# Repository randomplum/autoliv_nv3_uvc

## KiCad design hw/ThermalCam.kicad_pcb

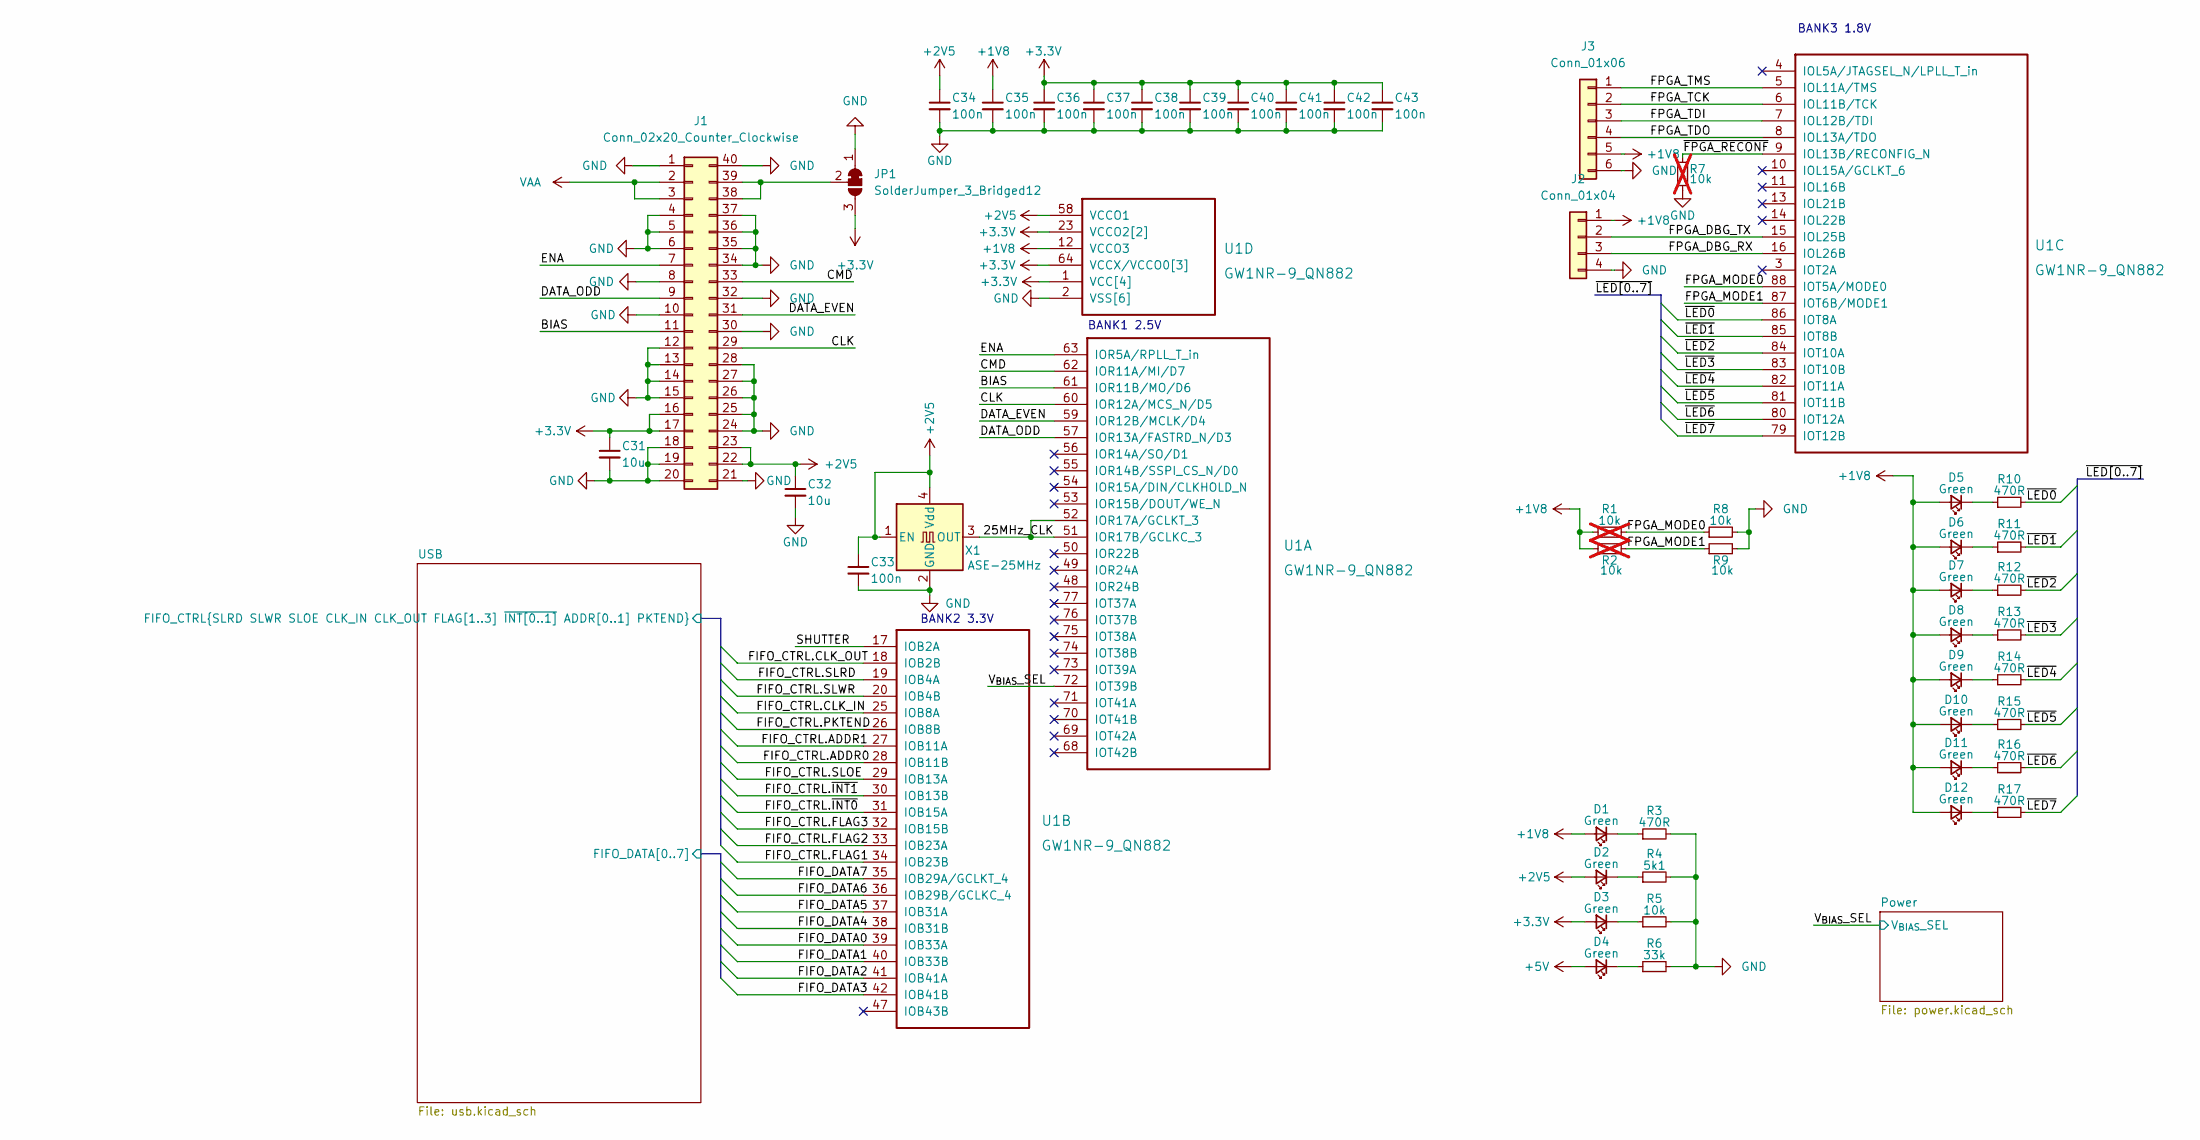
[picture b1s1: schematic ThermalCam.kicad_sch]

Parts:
C31, C32: 10u; C_0402_1005Metric
C33, C34, C35, C36, C37, C38, C39, C40, C41, C42, C43: 100n; C_0402_1005Metric
D1, D2, D3, D4, D5, D6, D7, D8, D9, D10, D11, D12: Green; LED_0402_1005Metric
J1: Conn_02x20_Counter_Clockwise; 52991-0408
J2: Conn_01x04; PinHeader_1x04_P2.54mm_Vertical
J3: Conn_01x06; PinHeader_1x06_P2.54mm_Vertical
JP1: SolderJumper_3_Bridged12; SolderJumper-3_P1.3mm_Bridged2Bar12_RoundedPad1.0x1.5mm_Num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
R1, R2, R7: 10k; R_0402_1005Metric; not fitted
R3, R10, R11, R12, R13, R14, R15, R16, R17: 470R; R_0402_1005Metric
R4: 5k1; R_0402_1005Metric
R5, R8, R9: 10k; R_0402_1005Metric
R6: 33k; R_0402_1005Metric
U1: GW1NR-9_QN882; QFN-88_EP_10x10_Pitch0.4mm
X1: ASE-25MHz; Oscillator_SMD_Abracon_ASE-4Pin_3.2x2.5mm

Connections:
+1V8: C35.1, D1.2 (A), D5.2 (A), D6.2 (A), D7.2 (A), D8.2 (A), D9.2 (A), D10.2 (A), D11.2 (A), D12.2 (A), J2.1, J3.5, R1.1, R2.1, U1.12 (VCCO3); also elsewhere on the board
+2V5: C32.1, C33.1, C34.1, D2.2 (A), J1.22, J1.23, U1.58 (VCCO1), X1.1 (EN), X1.4 (Vdd); also elsewhere on the board
+3.3V: C31.1, C36.1, C37.1, C38.1, C39.1, C40.1, C41.1, C42.1, C43.1, D3.2 (A), J1.16, J1.17, JP1.3 (B), U1.1 (VCC[4]), U1.22 (VCC[4]), U1.23 (VCCO2[2]), U1.44 (VCCO2[2]), U1.45 (VCC[4]), U1.64 (VCCX/VCCO0[3]), U1.66 (VCC[4]), U1.67 (VCCX/VCCO0[3]), U1.78 (VCCX/VCCO0[3]); also elsewhere on the board
+5V: D4.2 (A); also elsewhere on the board
/25MHz_CLK: U1.51 (IOR17B/GCLKC_3), U1.52 (IOR17A/GCLKT_3), X1.3 (OUT)
/BIAS: J1.11, U1.61 (IOR11B/MO/D6)
/CLK: J1.29, U1.60 (IOR12A/MCS_N/D5)
/CMD: J1.33, U1.62 (IOR11A/MI/D7)
/DATA_EVEN: J1.31, U1.59 (IOR12B/MCLK/D4)
/DATA_ODD: J1.9, U1.57 (IOR13A/FASTRD_N/D3)
/ENA: J1.7, U1.63 (IOR5A/RPLL_T_in)
/FPGA_DBG_RX: J2.3, U1.16 (IOL26B)
/FPGA_DBG_TX: J2.2, U1.15 (IOL25B)
/FPGA_MODE0: R1.2, R8.1, U1.88 (IOT5A/MODE0)
/FPGA_MODE1: R2.2, R9.1, U1.87 (IOT6B/MODE1)
/FPGA_TCK: J3.2, U1.6 (IOL11B/TCK)
/FPGA_TDI: J3.3, U1.7 (IOL12B/TDI)
/FPGA_TDO: J3.4, U1.8 (IOL13A/TDO)
/FPGA_TMS: J3.1, U1.5 (IOL11A/TMS)
/SHUTTER: U1.17 (IOB2A)
/USB/FIFO_CTRL.ADDR0: U1.28 (IOB11B); also elsewhere on the board
/USB/FIFO_CTRL.ADDR1: U1.27 (IOB11A); also elsewhere on the board
/USB/FIFO_CTRL.CLK_IN: U1.25 (IOB8A); also elsewhere on the board
/USB/FIFO_CTRL.CLK_OUT: U1.18 (IOB2B); also elsewhere on the board
/USB/FIFO_CTRL.FLAG1: U1.34 (IOB23B); also elsewhere on the board
/USB/FIFO_CTRL.FLAG2: U1.33 (IOB23A); also elsewhere on the board
/USB/FIFO_CTRL.FLAG3: U1.32 (IOB15B); also elsewhere on the board
/USB/FIFO_CTRL.PKTEND: U1.26 (IOB8B); also elsewhere on the board
/USB/FIFO_CTRL.SLOE: U1.29 (IOB13A); also elsewhere on the board
/USB/FIFO_CTRL.SLRD: U1.19 (IOB4A); also elsewhere on the board
/USB/FIFO_CTRL.SLWR: U1.20 (IOB4B); also elsewhere on the board
/USB/FIFO_CTRL.~INT0: U1.31 (IOB15A); also elsewhere on the board
/USB/FIFO_CTRL.~INT1: U1.30 (IOB13B); also elsewhere on the board
/USB/FIFO_DATA0: U1.39 (IOB33A); also elsewhere on the board
/USB/FIFO_DATA1: U1.40 (IOB33B); also elsewhere on the board
/USB/FIFO_DATA2: U1.41 (IOB41A); also elsewhere on the board
/USB/FIFO_DATA3: U1.42 (IOB41B); also elsewhere on the board
/USB/FIFO_DATA4: U1.38 (IOB31B); also elsewhere on the board
/USB/FIFO_DATA5: U1.37 (IOB31A); also elsewhere on the board
/USB/FIFO_DATA6: U1.36 (IOB29B/GCLKC_4); also elsewhere on the board
/USB/FIFO_DATA7: U1.35 (IOB29A/GCLKT_4); also elsewhere on the board
/V_{BIAS}_SEL: U1.72 (IOT39B); also elsewhere on the board
/~FPGA_RECONF: R7.1, U1.9 (IOL13B/RECONFIG_N)
/~LED0: R10.2, U1.86 (IOT8A)
/~LED1: R11.2, U1.85 (IOT8B)
/~LED2: R12.2, U1.84 (IOT10A)
/~LED3: R13.2, U1.83 (IOT10B)
/~LED4: R14.2, U1.82 (IOT11A)
/~LED5: R15.2, U1.81 (IOT11B)
/~LED6: R16.2, U1.80 (IOT12A)
/~LED7: R17.2, U1.79 (IOT12B)
GND: C31.2, C32.2, C33.2, C34.2, C35.2, C36.2, C37.2, C38.2, C39.2, C40.2, C41.2, C42.2, C43.2, J1.1, J1.4, J1.5, J1.6, J1.8, J1.10, J1.12, J1.13, J1.14, J1.15, J1.18, J1.19, J1.20, J1.21, J1.24, J1.25, J1.26, J1.27, J1.28, J1.30, J1.32, J1.34, J1.35, J1.36, J1.37, J1.40, J2.4, J3.6, JP1.1 (A), R3.2, R4.2, R5.2, R6.2, R7.2, R8.2, R9.2, U1.2 (VSS[6]), U1.21 (VSS[6]), U1.24 (VSS[6]), U1.43 (VSS[6]), U1.46 (VSS[6]), U1.65 (VSS[6]), U1.89 (VSS[6]), X1.2 (GND); also elsewhere on the board
unnamed: D1.1 (K), R3.1
unnamed: D2.1 (K), R4.1
unnamed: D3.1 (K), R5.1
unnamed: D4.1 (K), R6.1
unnamed: D5.1 (K), R10.1
unnamed: D6.1 (K), R11.1
unnamed: D7.1 (K), R12.1
unnamed: D8.1 (K), R13.1
unnamed: D9.1 (K), R14.1
unnamed: D10.1 (K), R15.1
unnamed: D11.1 (K), R16.1
unnamed: D12.1 (K), R17.1
unnamed: J1.38, J1.39, JP1.2 (C)
VAA: J1.2, J1.3; also elsewhere on the board

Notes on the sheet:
BANK3 1.8V
BANK1 2.5V
BANK2 3.3V

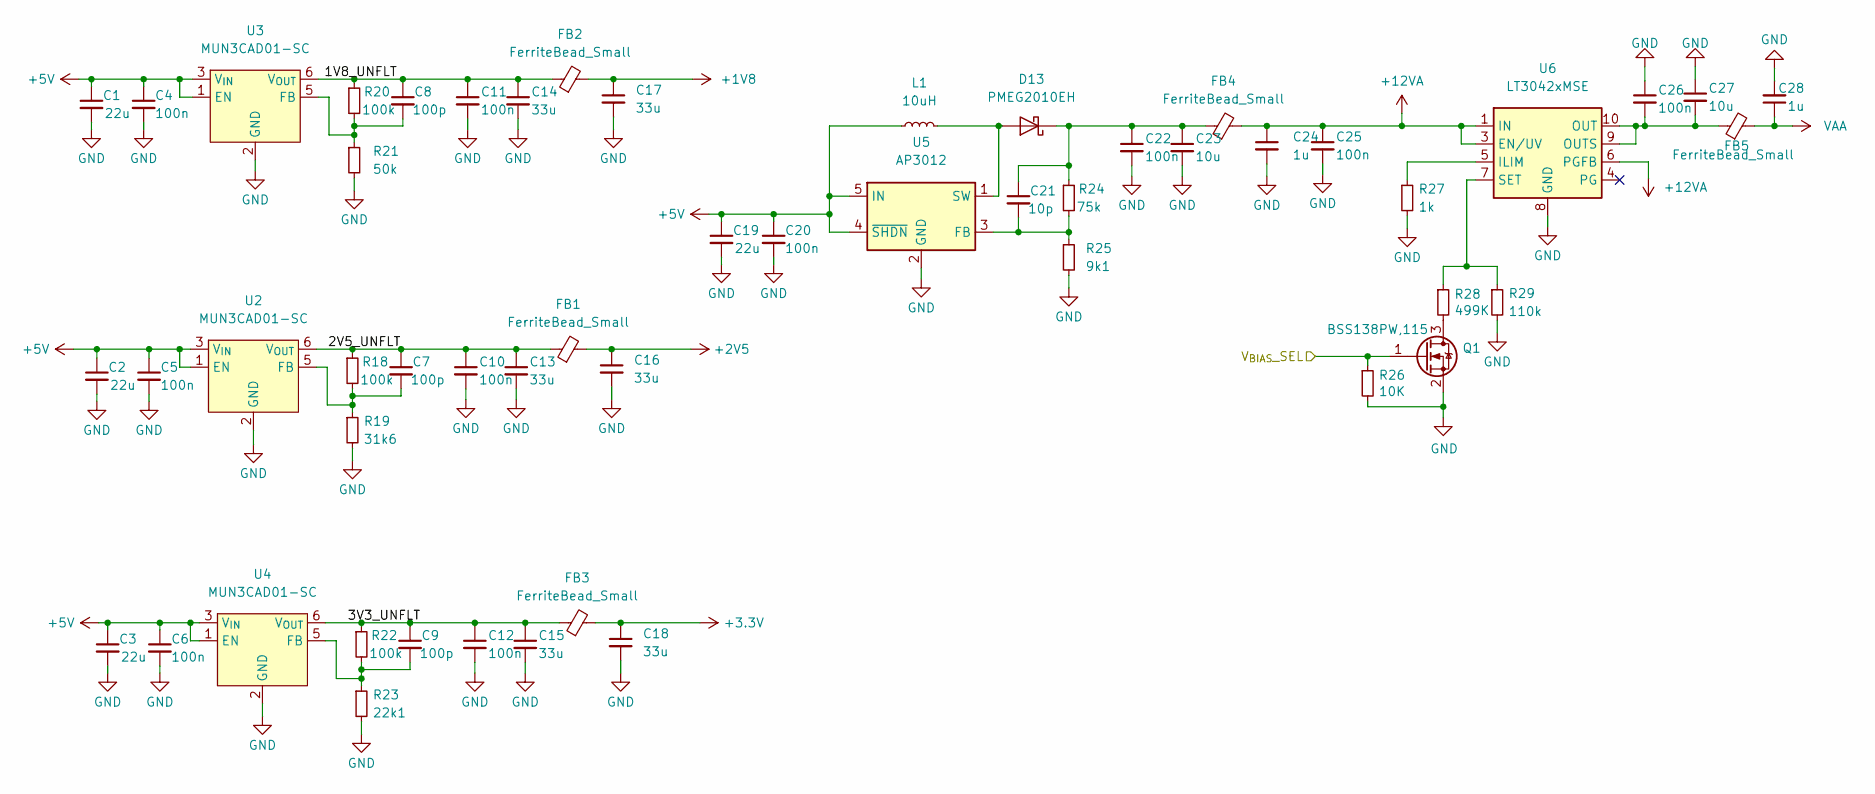
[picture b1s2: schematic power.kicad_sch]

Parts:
C1, C2, C3, C19: 22u; C_0805_2012Metric
C4, C5, C6, C10, C11, C12, C20, C22, C25, C26: 100n; C_0402_1005Metric
C7, C8, C9: 100p; C_0402_1005Metric
C13, C14, C15, C16, C17, C18: 33u; C_0805_2012Metric
C21: 10p; C_0402_1005Metric
C23, C27: 10u; C_0805_2012Metric
C24, C28: 1u; C_0805_2012Metric
D13: PMEG2010EH; D_SOD-123F
FB1, FB2, FB3, FB4, FB5: FerriteBead_Small; L_0603_1608Metric
L1: 10uH; L_1812_4532Metric
Q1: BSS138PW,115; SOT-323_SC-70; MPN BSS138PW,115
R18, R20, R22: 100k; R_0402_1005Metric
R19: 31k6; R_0402_1005Metric
R21: 50k; R_0402_1005Metric
R23: 22k1; R_0402_1005Metric
R24: 75k; R_0402_1005Metric
R25: 9k1; R_0402_1005Metric
R26: 10K; R_0402_1005Metric
R27: 1k; R_0402_1005Metric
R28: 499K; R_0402_1005Metric
R29: 110k; R_0402_1005Metric
U2, U3, U4: MUN3CAD01-SC; MUN3CAD01
U5: AP3012; SOT-23-5
U6: LT3042xMSE; MSOP-10-1EP_3x3mm_P0.5mm_EP1.68x1.88mm

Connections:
+1V8: C17.1, FB2.2; also elsewhere on the board
+2V5: C16.1, FB1.2; also elsewhere on the board
+3.3V: C18.1, FB3.2; also elsewhere on the board
+5V: C1.1, C2.1, C3.1, C4.1, C5.1, C6.1, C19.1, C20.1, L1.1, U2.1 (EN), U2.3 (V_{IN}), U3.1 (EN), U3.3 (V_{IN}), U4.1 (EN), U4.3 (V_{IN}), U5.4 (~SHDN), U5.5 (IN); also elsewhere on the board
+12VA: C24.1, C25.1, FB4.2, U6.1 (IN), U6.2 (IN), U6.3 (EN/UV), U6.6 (PGFB)
/Power/1V8_UNFLT: C8.1, C11.1, C14.1, FB2.1, R20.1, U3.6 (V_{OUT})
/Power/2V5_UNFLT: C7.1, C10.1, C13.1, FB1.1, R18.1, U2.6 (V_{OUT})
/Power/3V3_UNFLT: C9.1, C12.1, C15.1, FB3.1, R22.1, U4.6 (V_{OUT})
/V_{BIAS}_SEL: Q1.1 (G), R26.1; also elsewhere on the board
GND: C1.2, C2.2, C3.2, C4.2, C5.2, C6.2, C10.2, C11.2, C12.2, C13.2, C14.2, C15.2, C16.2, C17.2, C18.2, C19.2, C20.2, C22.2, C23.2, C24.2, C25.2, C26.1, C27.1, C28.2, Q1.2 (S), R19.2, R21.2, R23.2, R25.2, R26.2, R27.2, R29.2, U2.2 (GND), U2.4 (GND), U3.2 (GND), U3.4 (GND), U4.2 (GND), U4.4 (GND), U5.2 (GND), U6.8 (GND), U6.11 (GND); also elsewhere on the board
unnamed: D13.2 (A), L1.2, U5.1 (SW)
unnamed: C21.1, C22.1, C23.1, D13.1 (K), FB4.1, R24.1
unnamed: Q1.3 (D), R28.2
unnamed: C7.2, R18.2, R19.1, U2.5 (FB)
unnamed: C8.2, R20.2, R21.1, U3.5 (FB)
unnamed: C9.2, R22.2, R23.1, U4.5 (FB)
unnamed: C21.2, R24.2, R25.1, U5.3 (FB)
unnamed: R27.1, U6.5 (ILIM)
unnamed: C26.2, C27.2, FB5.1, U6.9 (OUTS), U6.10 (OUT)
unnamed: R28.1, R29.1, U6.7 (SET)
VAA: C28.1, FB5.2; also elsewhere on the board

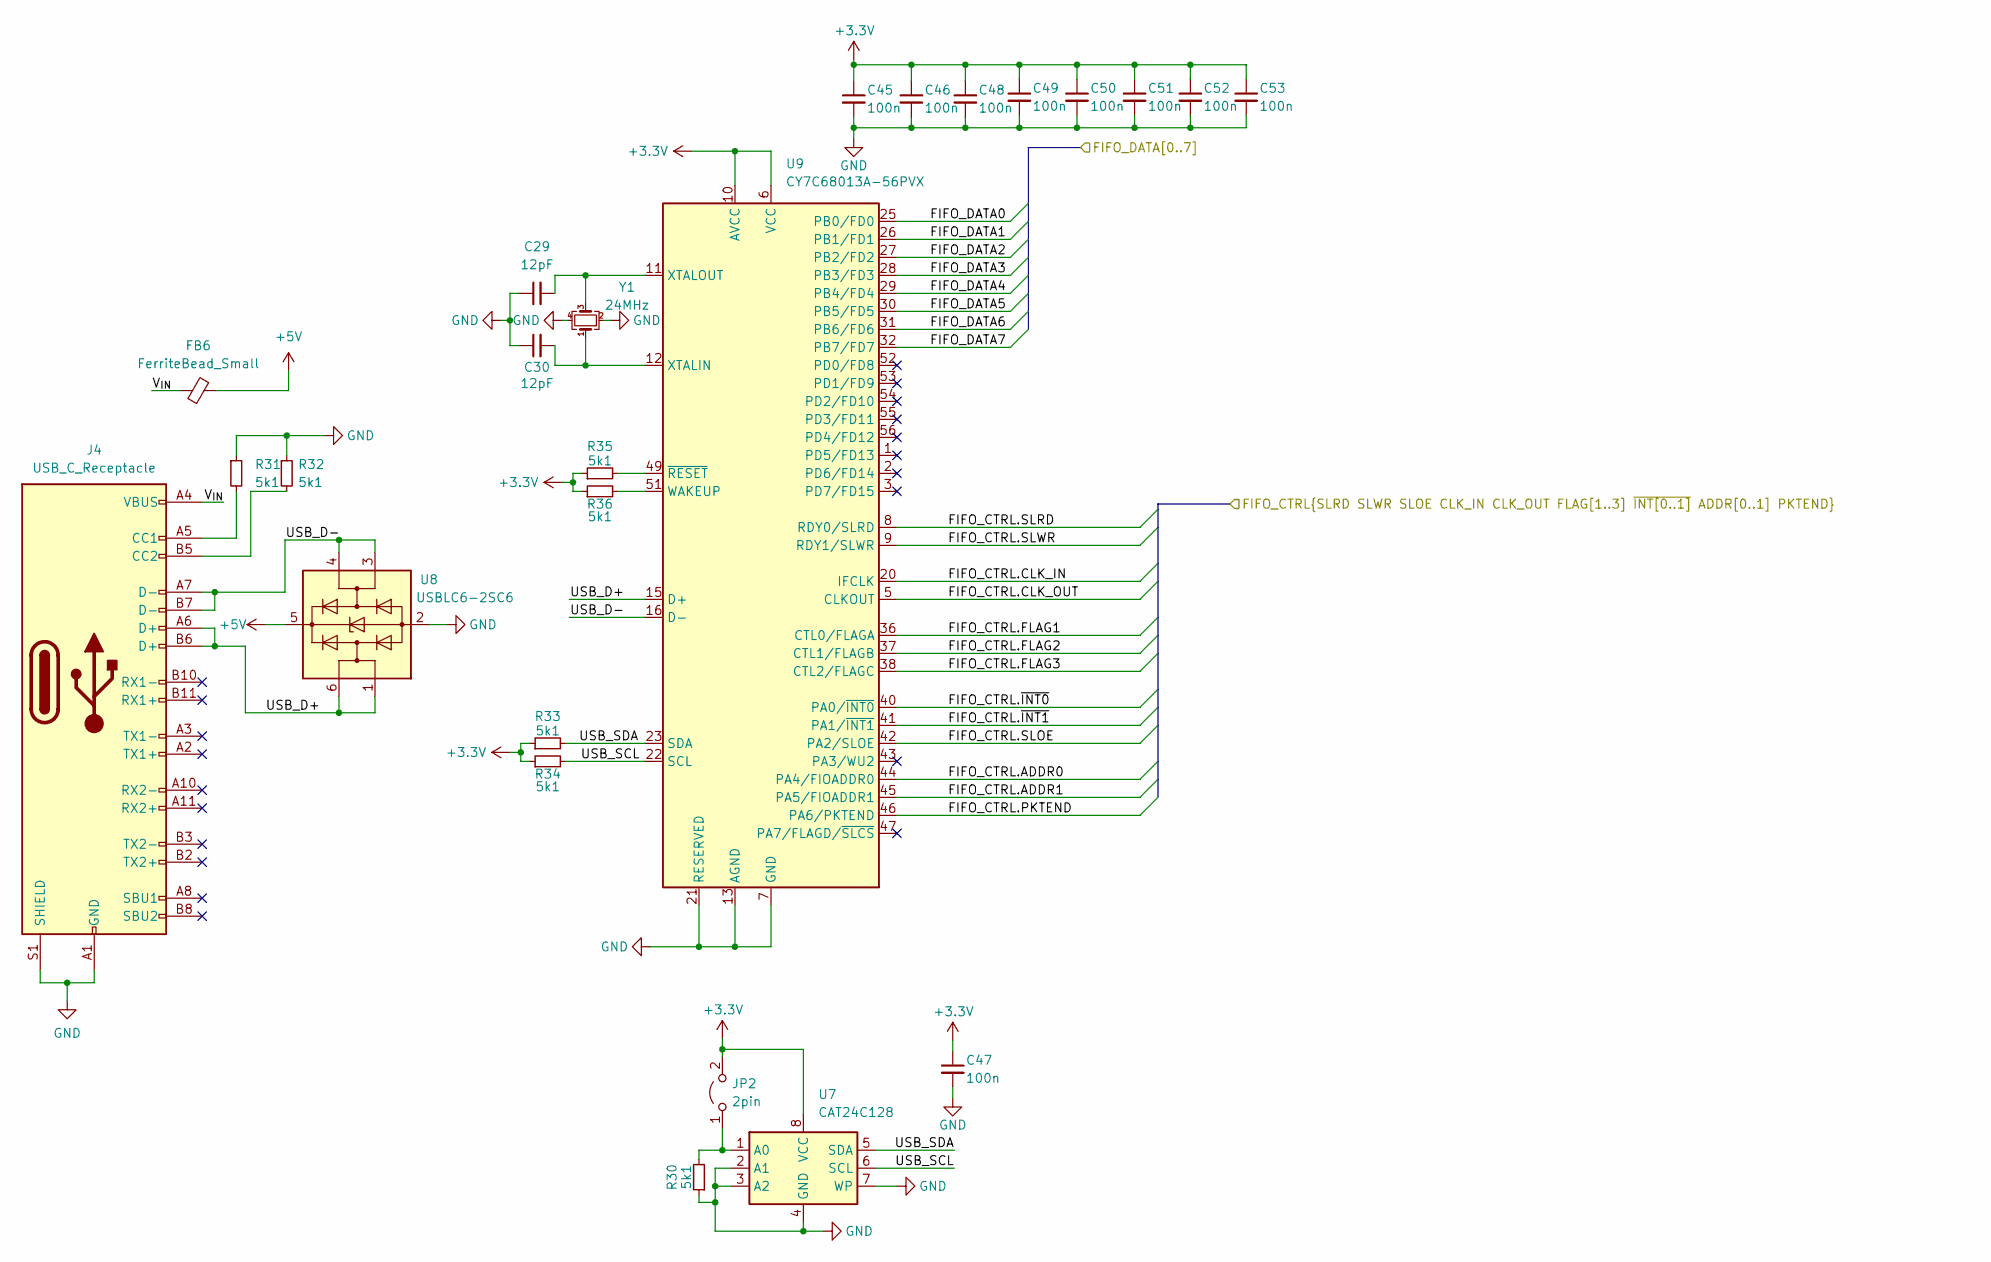
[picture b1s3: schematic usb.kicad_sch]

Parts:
C29, C30: 12pF; C_0402_1005Metric
C45, C46, C47, C48, C49, C50, C51, C52, C53: 100n; C_0402_1005Metric
FB6: FerriteBead_Small; L_0603_1608Metric
J4: USB_C_Receptacle; USB_C_Receptacle_JAE_DX07S024WJ3R400
JP2: 2pin; PinHeader_1x02_P2.54mm_Vertical
R30, R31, R32, R33, R34, R35, R36: 5k1; R_0402_1005Metric
U7: CAT24C128; TSSOP-8_4.4x3mm_P0.65mm
U8: USBLC6-2SC6; SOT-23-6
U9: CY7C68013A-56PVX; SSOP-56_7.5x18.5mm_P0.635mm
Y1: 24MHz; Crystal_SMD_Abracon_ABM8G-4Pin_3.2x2.5mm

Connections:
+3.3V: C45.1, C46.1, C47.1, C48.1, C49.1, C50.1, C51.1, C52.1, C53.1, JP2.2 (B), R33.1, R34.1, R35.1, R36.1, U7.8 (VCC), U9.6 (VCC), U9.10 (AVCC), U9.14 (AVCC), U9.18 (VCC), U9.24 (VCC), U9.34 (VCC), U9.39 (VCC), U9.50 (VCC); also elsewhere on the board
+5V: FB6.2, U8.5 (VBUS); also elsewhere on the board
/USB/FIFO_CTRL.ADDR0: U9.44 (PA4/FIOADDR0); also elsewhere on the board
/USB/FIFO_CTRL.ADDR1: U9.45 (PA5/FIOADDR1); also elsewhere on the board
/USB/FIFO_CTRL.CLK_IN: U9.20 (IFCLK); also elsewhere on the board
/USB/FIFO_CTRL.CLK_OUT: U9.5 (CLKOUT); also elsewhere on the board
/USB/FIFO_CTRL.FLAG1: U9.36 (CTL0/FLAGA); also elsewhere on the board
/USB/FIFO_CTRL.FLAG2: U9.37 (CTL1/FLAGB); also elsewhere on the board
/USB/FIFO_CTRL.FLAG3: U9.38 (CTL2/FLAGC); also elsewhere on the board
/USB/FIFO_CTRL.PKTEND: U9.46 (PA6/PKTEND); also elsewhere on the board
/USB/FIFO_CTRL.SLOE: U9.42 (PA2/SLOE); also elsewhere on the board
/USB/FIFO_CTRL.SLRD: U9.8 (RDY0/SLRD); also elsewhere on the board
/USB/FIFO_CTRL.SLWR: U9.9 (RDY1/SLWR); also elsewhere on the board
/USB/FIFO_CTRL.~INT0: U9.40 (PA0/~INT0); also elsewhere on the board
/USB/FIFO_CTRL.~INT1: U9.41 (PA1/~INT1); also elsewhere on the board
/USB/FIFO_DATA0: U9.25 (PB0/FD0); also elsewhere on the board
/USB/FIFO_DATA1: U9.26 (PB1/FD1); also elsewhere on the board
/USB/FIFO_DATA2: U9.27 (PB2/FD2); also elsewhere on the board
/USB/FIFO_DATA3: U9.28 (PB3/FD3); also elsewhere on the board
/USB/FIFO_DATA4: U9.29 (PB4/FD4); also elsewhere on the board
/USB/FIFO_DATA5: U9.30 (PB5/FD5); also elsewhere on the board
/USB/FIFO_DATA6: U9.31 (PB6/FD6); also elsewhere on the board
/USB/FIFO_DATA7: U9.32 (PB7/FD7); also elsewhere on the board
/USB/USB_D+: J4.A6 (D+), J4.B6 (D+), U8.1 (I/O1), U8.6 (I/O1), U9.15 (D+)
/USB/USB_D-: J4.A7 (D-), J4.B7 (D-), U8.3 (I/O2), U8.4 (I/O2), U9.16 (D-)
/USB/USB_SCL: R34.2, U7.6 (SCL), U9.22 (SCL)
/USB/USB_SDA: R33.2, U7.5 (SDA), U9.23 (SDA)
/USB/V_{IN}: FB6.1, J4.A4 (VBUS), J4.A9 (VBUS), J4.B4 (VBUS), J4.B9 (VBUS)
GND: C29.1, C30.1, C45.2, C46.2, C47.2, C48.2, C49.2, C50.2, C51.2, C52.2, C53.2, J4.A1 (GND), J4.A12 (GND), J4.B1 (GND), J4.B12 (GND), J4.S1 (SHIELD), R30.1, R31.1, R32.1, U7.2 (A1), U7.3 (A2), U7.4 (GND), U7.7 (WP), U8.2 (GND), U9.4 (GND), U9.7 (GND), U9.13 (AGND), U9.17 (AGND), U9.19 (GND), U9.21 (RESERVED), U9.33 (GND), U9.35 (GND), U9.48 (GND), Y1.2, Y1.4; also elsewhere on the board
unnamed: J4.A5 (CC1), R31.2
unnamed: J4.B5 (CC2), R32.2
unnamed: JP2.1 (A), R30.2, U7.1 (A0)
unnamed: R36.2, U9.51 (WAKEUP)
unnamed: C30.2, U9.12 (XTALIN), Y1.1
unnamed: C29.2, U9.11 (XTALOUT), Y1.3
unnamed: R35.2, U9.49 (~RESET)

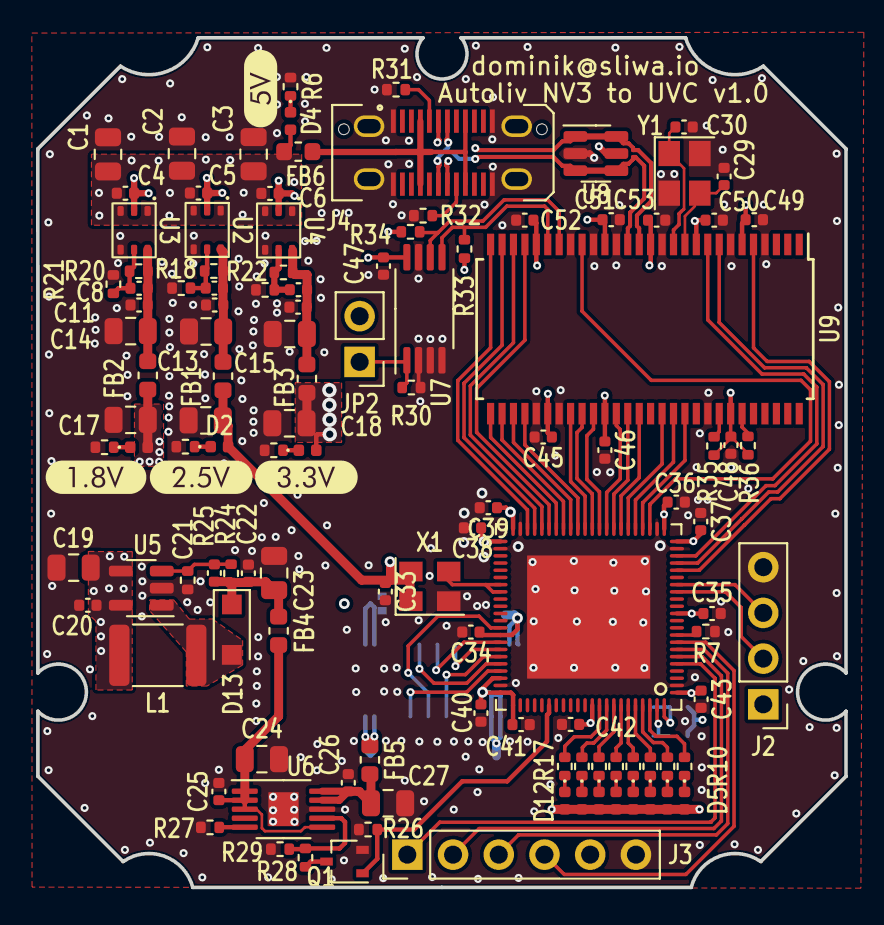
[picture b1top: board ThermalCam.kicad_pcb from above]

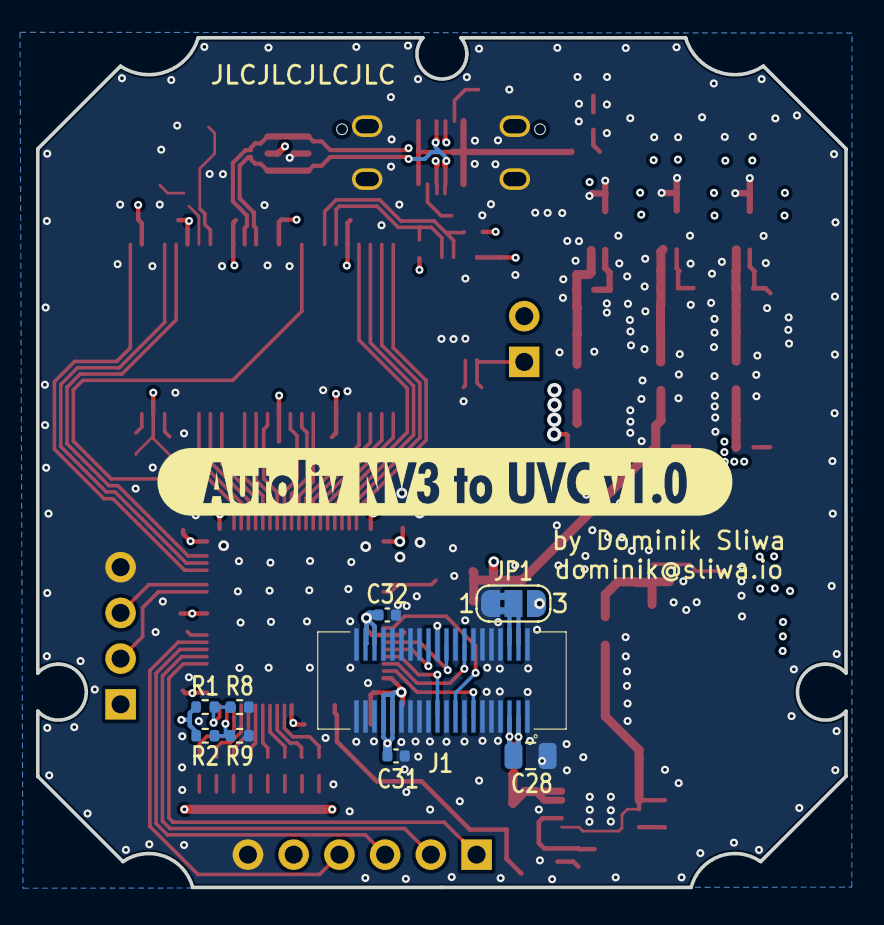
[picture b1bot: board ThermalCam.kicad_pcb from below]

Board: 4 copper layers, 44.9 x 47.2 mm, 131 parts (10 on the bottom side), 91 nets.

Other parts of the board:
kibuzzard-636D73F4: G***; kibuzzard-636D73F4
kibuzzard-636D765E: G***; kibuzzard-636D765E
kibuzzard-636D7417: G***; kibuzzard-636D7417
kibuzzard-636D7427: G***; kibuzzard-636D7427
kibuzzard-636D7435: G***; kibuzzard-636D7435

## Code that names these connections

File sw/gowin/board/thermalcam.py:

import os
import subprocess

from amaranth.build import Subsignal, Resource, Clock, Pins, Attrs
from amaranth.vendor.gowin import GowinPlatform
from amaranth_boards.resources import LEDResources, UARTResource


__all__ = ["ThermalCamPlatform"]


def PSRAMResouce(*args, dq, rwds, ck, ck_n, cs_n, reset_n, attrs=None,
                 conn=None):

    io = []
    io.append(Subsignal("dq", Pins(dq, dir="io", conn=conn, assert_width=8)))
    io.append(Subsignal("rwds", Pins(rwds, dir="io", conn=conn,
                                     assert_width=1)))
    io.append(Subsignal("ck", Pins(ck, dir="o", conn=conn, assert_width=1)))
    io.append(Subsignal("ck_n", Pins(ck_n, dir="o", conn=conn,
                                     assert_width=1)))
    io.append(Subsignal("cs_n", Pins(cs_n, dir="o", conn=conn,
                                     assert_width=1)))
    io.append(Subsignal("reset_n", Pins(reset_n, dir="o", conn=conn,
                                        assert_width=1)))
    if attrs is not None:
        io.append(attrs)
    return Resource.family(*args, default_name="psram", ios=io)


def FIFOResource(*args, data, clk_out, addr, sloe, slrd, slwr, pktend, full,
                 empty, data_dir='o', clk_dir='o', attrs=None, con=None):
    assert clk_dir in ('i', 'o',)
    assert data_dir in ('i', 'o', 'io',)

    io = []
    io.append(Subsignal("data", Pins(data, dir="o", conn=con, assert_width=8)))
    io.append(Subsignal("addr", Pins(addr, dir="o", conn=con, assert_width=2)))
    io.append(Subsignal("clk_out", Pins(
        clk_out, dir=clk_dir, conn=con, assert_width=1)))
    io.append(Subsignal("sloe", Pins(sloe, dir="o", conn=con, assert_width=1)))
    io.append(Subsignal("slrd", Pins(slrd, dir="o", conn=con, assert_width=1)))
    io.append(Subsignal("slwr", Pins(slwr, dir="o", conn=con, assert_width=1)))
    io.append(Subsignal("pktend", Pins(
        pktend, dir="o", conn=con, assert_width=1)))
    io.append(Subsignal("full", Pins(full, dir="i", conn=con, assert_width=1)))
    io.append(Subsignal("empty", Pins(empty, dir="i", conn=con,
                                      assert_width=1)))
    if attrs is not None:
        io.append(attrs)
    return Resource.family(*args, default_name="fifo", ios=io)


def NV3Resource(*args, clk, cmd, ena, bias, data_even, data_odd, attrs=None,
                con=None):

    io = []
    io.append(Subsignal("clk_t", Pins(clk, dir="o", conn=con, assert_width=1)))
    io.append(Subsignal("cmd_t", Pins(cmd, dir="o", conn=con, assert_width=1)))
    io.append(Subsignal("ena_t", Pins(ena, dir="o", conn=con, assert_width=1)))
    io.append(Subsignal("bias_t", Pins(bias, dir="o", conn=con,
                        assert_width=1)))
    io.append(Subsignal("data_even_t", Pins(
        data_even, dir="io", conn=con, assert_width=1)))
    io.append(Subsignal("data_odd_t", Pins(
        data_odd, dir="io", conn=con, assert_width=1)))
    if attrs is not None:
        io.append(attrs)
    return Resource.family(*args, default_name="nv3", ios=io)


class ThermalCamPlatform(GowinPlatform):
    part = "GW1NR-UV9QN88PC6/I5"
    family = "GW1NR-9"
    # default_clk = "clk25"
    resources = [
        Resource("clk25", 0, Pins("52", dir="i"),
                 Clock(25e6), Attrs(IO_TYPE="LVCMOS25")),

        *LEDResources(pins="86 85 84 83 82 81 80 79",
                      attrs=Attrs(IO_TYPE="LVCMOS18")),

        UARTResource(0,
                     rx="16", tx="15",
                     attrs=Attrs(IO_TYPE="LVCMOS18", PULLUP=1),
                     role="dce"
                     ),
        FIFOResource(0,
                     data="39 40 41 42 38 37 36 35", addr="28 27",
                     clk_out="25", sloe="29", slrd="19", slwr="20",
                     pktend="26", full="33", empty="32",
                     attrs=Attrs(IO_TYPE="LVCMOS33")
                     ),
        PSRAMResouce(0,
                     dq="IOL2B IOL3A IOL3B IOL4A IOL9A IOL14A IOL16A IOL17B",
                     rwds="IOL17A", ck="IOL8A", ck_n="IOL7A", cs_n="IOL6B",
                     reset_n="IOL2A", attrs=Attrs(IO_TYPE="LVCMOS18")
                     ),
        NV3Resource(0, clk="60", cmd="62", ena="63", bias="61", data_even="59",
                    data_odd="57"),

    ]
    connectors = [
    ]

    def toolchain_program(self, products, name):
        open_fpga_loader = os.environ.get("openFPGALoader", "openFPGALoader")
        with products.extract("{}.fs".format(name)) as bitstream_filename:
            subprocess.check_call(
                [open_fpga_loader, "-c", "tigard", bitstream_filename])


if __name__ == "__main__":
    from amaranth_boards.test.blinky import Blinky
    ThermalCamPlatform().build(Blinky(), do_program=True)

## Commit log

2022-11-07 ThermalCam: initial schematics
2022-11-10 add gowin fpga symbol library
2022-11-10 Autoliv NV3 to UVC v1.0
2023-07-08 schematic fixes and adding sw section
2023-07-08 sw: fx2: initial fx2 fw from HDMI2usb project
2023-07-08 sw: fx2: minimize code, remove cdc
2023-07-08 q: fx2: sdcc 4.3.0 fixes
2023-07-08 sw: fx2: move to bulk transfer over EP2
2023-07-12 working UVC demo
2023-07-12 remove fpga build dir
2023-07-12 add .gitignore
2023-09-24 Update to use mainline Amaranth gowin support
2023-09-25 Match the camera frame size in the USB descriptor
2023-09-25 add NV3 resource to the board file
2023-09-25 [experiments] playing with UVC...
2023-09-25 update .gitignore to ignore simulation results
2023-09-25 new fifo fsm
